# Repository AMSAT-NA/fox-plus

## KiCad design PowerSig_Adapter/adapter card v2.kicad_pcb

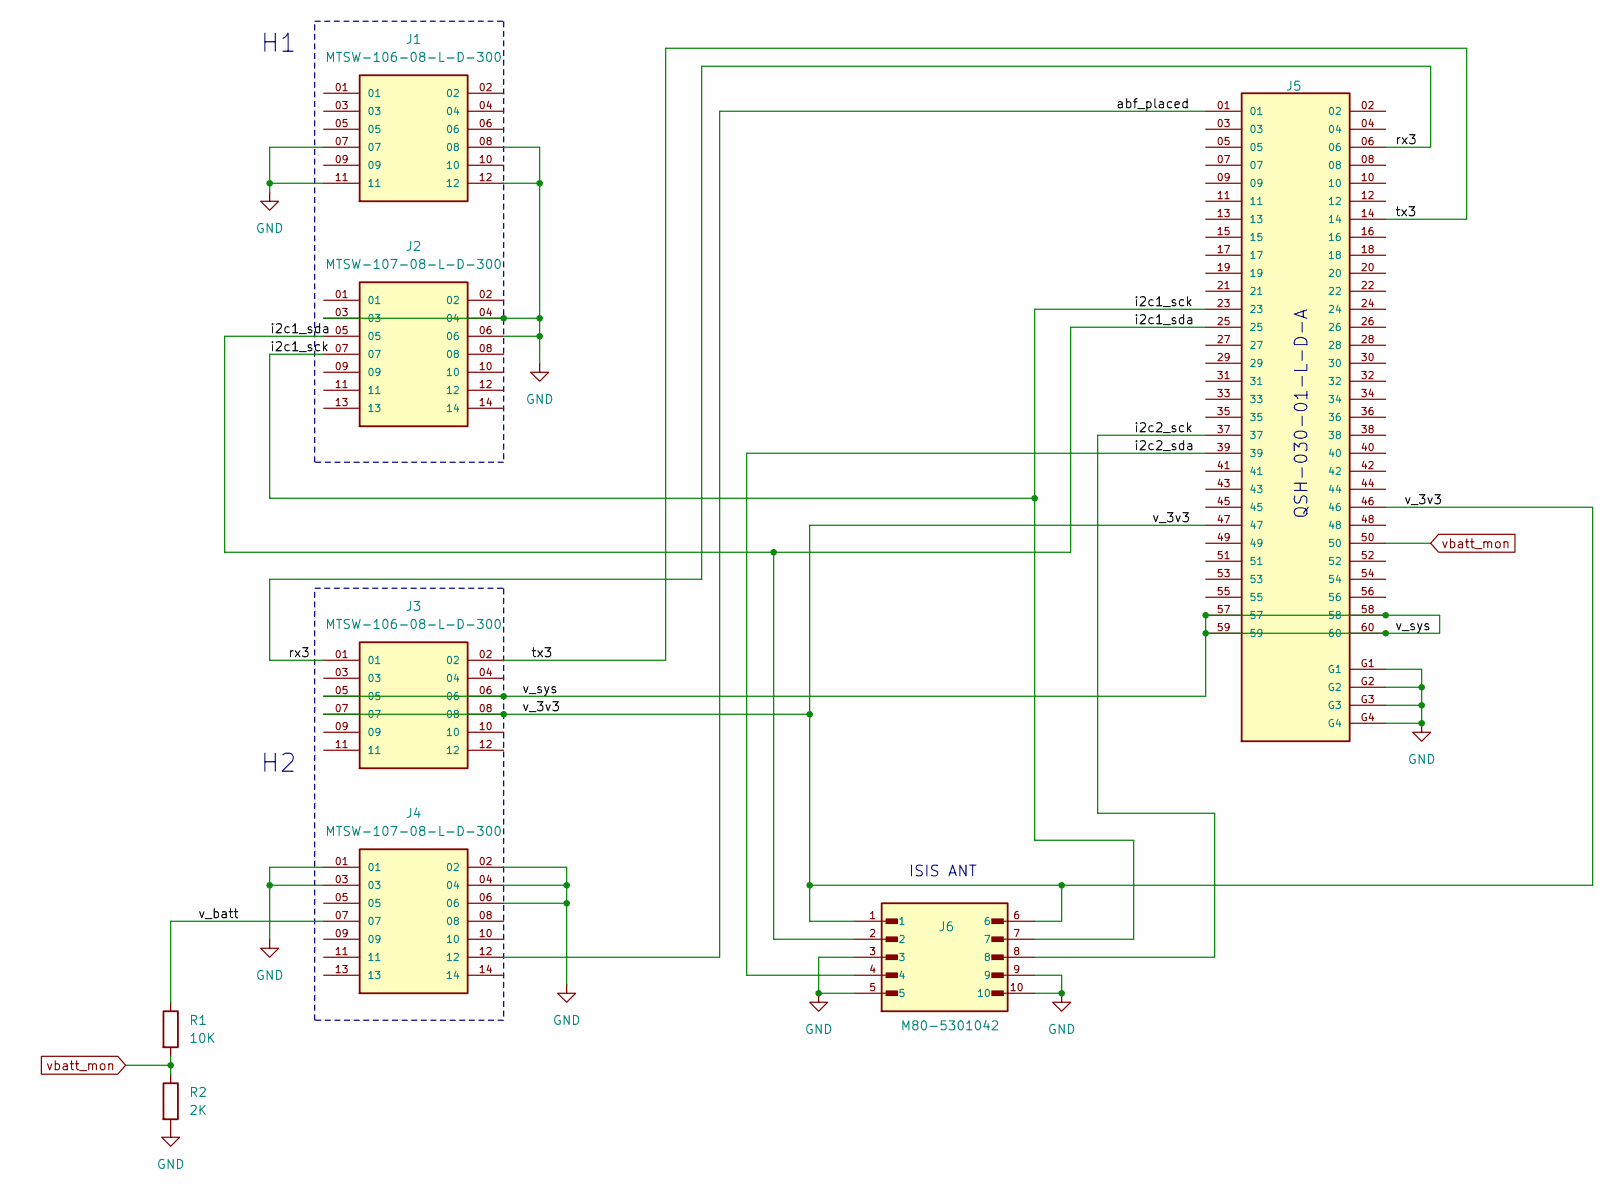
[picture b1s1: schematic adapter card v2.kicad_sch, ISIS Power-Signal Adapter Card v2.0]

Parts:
J1, J3: MTSW-106-08-L-D-300; SAMTEC_MTSW-106-X-X-D-X; PARTREV A
J2, J4: MTSW-107-08-L-D-300; SAMTEC_MTSW-107-08-L-D-300; PARTREV R
J5: QSH-030-01-X-D-A; SAMTEC_QSH-030-01-X-D-A-XX; PARTREV M
J6: M80-5301042; HARWIN_M80-5301042
R1: 10K; R_0603_1608Metric_Pad0.98x0.95mm_HandSolder
R2: 2K; R_0603_1608Metric_Pad0.98x0.95mm_HandSolder

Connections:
/abf_placed: J4.12, J5.01
/i2c1_sck: J2.07, J5.23, J6.7
/i2c1_sda: J2.05, J5.25, J6.2
/i2c2_sck: J5.37, J6.8
/i2c2_sda: J5.39, J6.4
/rx3: J3.01, J5.06
/tx3: J3.02, J5.14
/v_3v3: J3.07, J3.08, J5.46, J5.47, J6.1, J6.6
/v_batt: J4.07, R1.1
/v_sys: J3.05, J3.06, J5.57, J5.58, J5.59, J5.60
GND: J1.07, J1.08, J1.11, J1.12, J2.03, J2.04, J2.06, J4.01, J4.02, J4.03, J4.04, J4.06, J5.G1, J5.G2, J5.G3, J5.G4, J6.3, J6.5, J6.9, J6.10, R2.2
vbatt_mon: J5.50, R1.2, R2.1

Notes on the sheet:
ISIS ANT
QSH-030-01-L-D-A

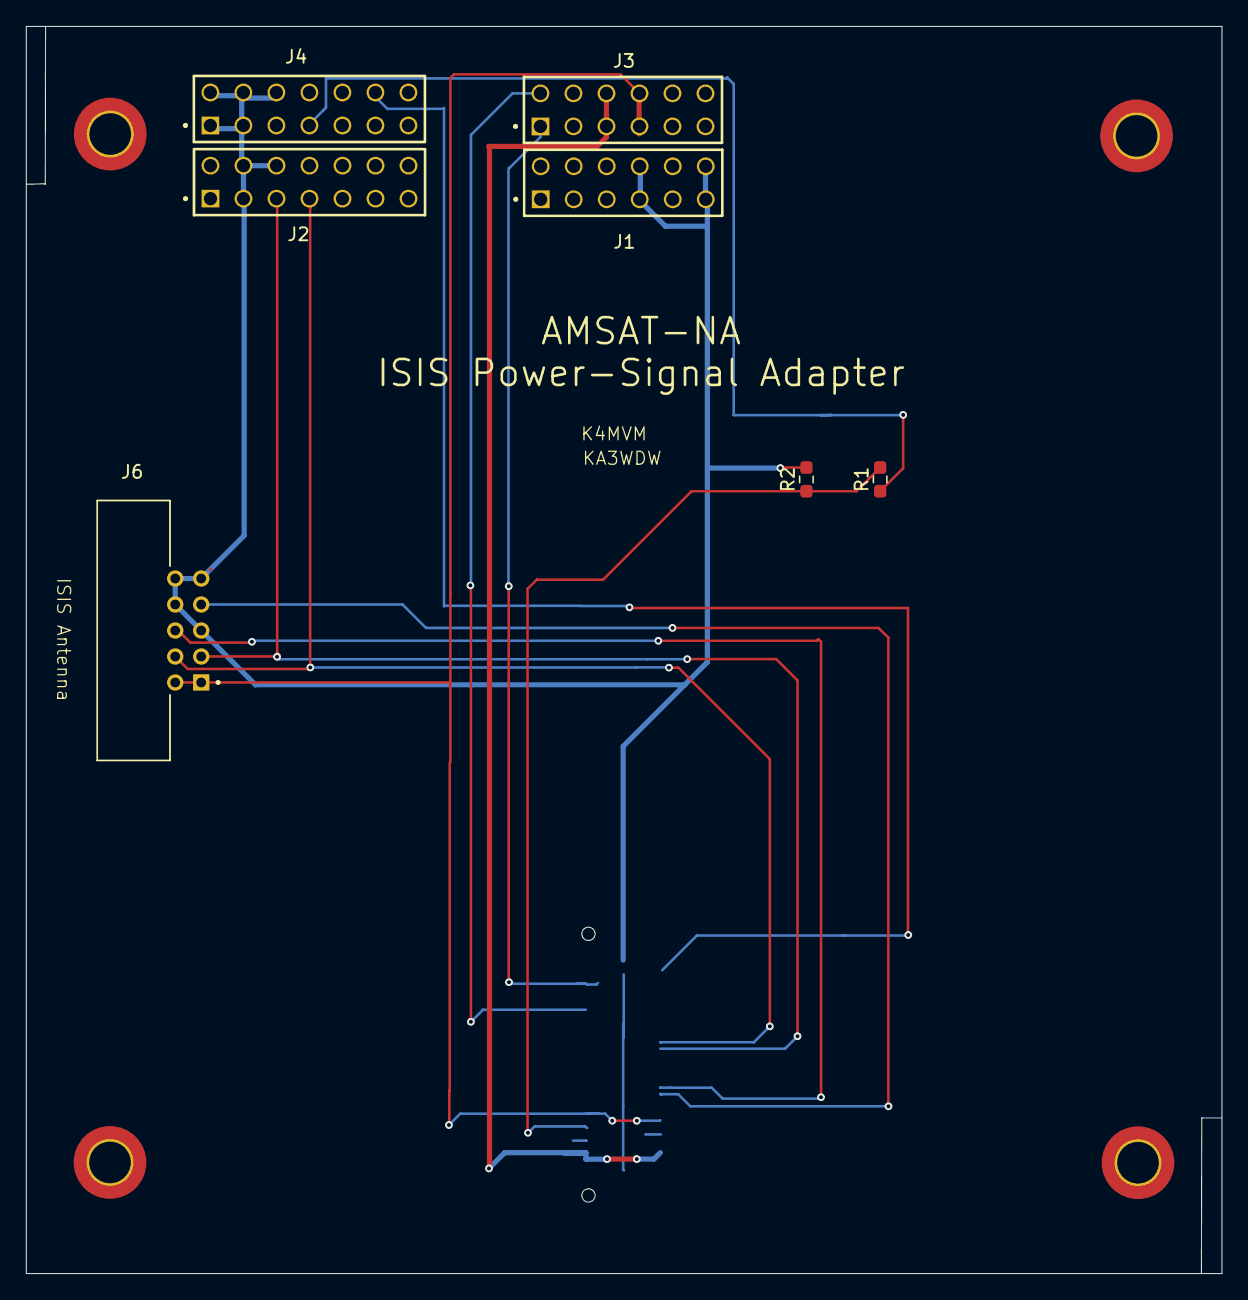
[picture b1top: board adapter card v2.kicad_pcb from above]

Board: 2 copper layers, 92.0 x 96.0 mm, 12 parts (1 on the bottom side), 12 nets.

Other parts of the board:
REF01, REF01#2, REF01#3, REF01#4: MountingHole_3.2mm_M3_DIN965_Pad_TopBottom

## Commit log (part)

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2022-02-24 Add initial CONOPS document
2022-02-24 Add Engineering Process document
2022-06-29 Upload some long overdue presentations
2022-06-30 Upload new weekly meeting presentation
2022-07-07 Upload another weekly engineering presentation
2022-07-21 Add presentations for weekly engineering meetings
2022-08-12 Add recent engineering meeting slides
2022-08-16 Update CONOPS
2022-08-16 Add this week's engineering presentation
2022-09-02 Add fox-plus structure files, engineering meeting presentations, and initial requirements spec
2022-09-29 Periodic update
2022-10-05 Push new SRS draft, new weekly engineering presentation
2022-12-07 Add weekly engineering presentations & structure model
2022-12-07 Add weekly_engineering_meetings
2022-12-22 Update SRS, add engineering meeting slides
2023-01-04 Add SRS v1.1
2023-01-12 Add new meeting presentations
2023-02-08 Add more weekly engineering meetign presentations
2023-02-16 Weekly engineering slides, FoxPlus-A power budget
2023-02-19 Update 1U structure adapter. Add block diagram. Add ISISPACE options sheets
2023-03-16 Add new weekly presentations, draft buss diagrams, bug ICR BOM
2023-03-16 Depending on Git rather than version numbers in filename
2023-03-16 Update Fox-Plus bus
2023-03-16 Add next week slides
2023-04-03 Create Compliance - Testing
2023-04-04 Delete Compliance - Testing
    File not needed. Just learning to use github....
2023-04-04 Add files via upload
    Fox-1E docs
2023-04-05 Update weekly engineering files
2023-04-05 Remove deprecated weekly engineering presentation
2023-04-12 Update latest weekly engineering presentations
2023-04-19 New weekly engineering presentation
2023-04-27 Update weekly engineering presentations
2023-05-03 Add files via upload
    overdue upload of Fox-Plus SRS v1.1
2023-05-04 Add files via upload
    Legacy IHU, LTM ICD
2023-05-05 Add weekly engineering presentation and 1U frame update
2023-05-24 Add weekly engineering presentations
2023-06-10 Add more weekly engineering presentations and update Fox-Plus structure model
2023-07-05 Add more weekly engineering presentations
2024-01-06 High level design notes + diagram
    Notes and diagram to prepare for PDR
2024-04-21 Add README.md
2024-04-21 Add coordinate system PPT strawman.
2024-04-21 Add folders
2024-04-21 Add assembly model and associated part models
2024-04-24 Add MEL and Coordinate Document strawman.
2024-04-24 Add EPS model to folder.
2024-04-24 Update SV Model with ISISpace EPS.
2024-04-25 Model updates, add templates, add drawing book
2024-04-28 Update to SV mechanical model
2024-04-29 Update drawing book, ME plan, and MEL
2024-04-29 Model updates and cleanups
2024-05-01 Update model layout per Mike's email.
2024-05-08 Update board model associations
2024-05-20 Update model with ISISpace solar panels.
2024-06-20 Add files via upload
    this is a preliminary version of the LIHU v2.4. It needs to be verified .
2024-10-15 Added Fox Mechanical List and FOX-ME-201 drawing
2024-12-23 Create Misc
2025-03-06 Add files via upload
    PSR#2
2025-08-02 Added initial release of Adapter PCB drawing
2025-08-02 FOX-ME-204 added to drawing list
2025-08-10 FOX-ME-204 Adapter PCB drawing added
2025-08-10 Update to Coordinate System PPT
2025-08-10 Mechanical folder cleanup - deleted duplicate PPT and out-of-date model
2025-08-10 Added McMaster Carr spec sheets for applicable hardware
2025-08-11 Update to SV Coordinate System document
2025-08-18 Learning git upload, first timer
2025-08-30 Added info and tracker for recent mechanical orders
2025-09-01 Update FOX-ME-204 adapter drawing
2025-09-02 Added Fox Plus Mechanical presentations to appropriate folder
2025-10-18 Added Robinson's 2025 Symposium presentation.
2025-10-20 Mike K4MVM presentations/2025 Symposium/FoxPlus Symposium 2025.pptx
2025-10-20 Adding 2024 Symposium Fox+ slides Signed-off-by: Mike Moore <k4mvm.22@gmail.com>
2025-11-02 Adding PSA v3
2025-11-05 Corrected schematic
2025-11-22 New spreadsheet for FoxPlus-A Cables & Connectors
2025-12-01 4 layer PSA board pdf and KiCad zip
2025-12-01 deleting files superseded by new version
2025-12-10 4 layer PSA revised with corrections
2025-12-10 Deleted rather than archived past versions of PSA board
2025-12-13 v1.3 only differs from v1.2 in that the resistors and capacitors are 0805
2026-01-17 FoxPlus-A Development Milestones for PDR
2026-01-17 Moved files from erroneous PDR folder
2026-01-17 corrections, renamed folder
2026-01-17 renamed folder
2026-01-17 correcting files
2026-01-17 file corrections
2026-01-25 new pdr folder
2026-01-26 Delete presentations/Project Reviews/Fox+ PDR Jan_2026 directory
    All PDR moved
2026-01-27 Dave update
2026-01-28 corrections. acronyms link.
2026-01-29 Public
2026-02-02 updated for PDR part 2
2026-02-06 adding open issues for comments
2026-02-19 Added umbilical PPT/PDF slides
2026-03-04 Delete PowerSig_Adapter/PowerSig_Adapter_v1.3.zip
    This file no longer valid
2026-03-04 ISIS Signals used on PSA
2026-03-12 Add files via upload
    Harwin 26p Connector
2026-03-17 Add files via upload
    Latest version PSA v1.2
2026-03-17 Delete PowerSig_Adapter/PowerSigAdapter_v1.2.pdf
    Obsolete - new version posted
